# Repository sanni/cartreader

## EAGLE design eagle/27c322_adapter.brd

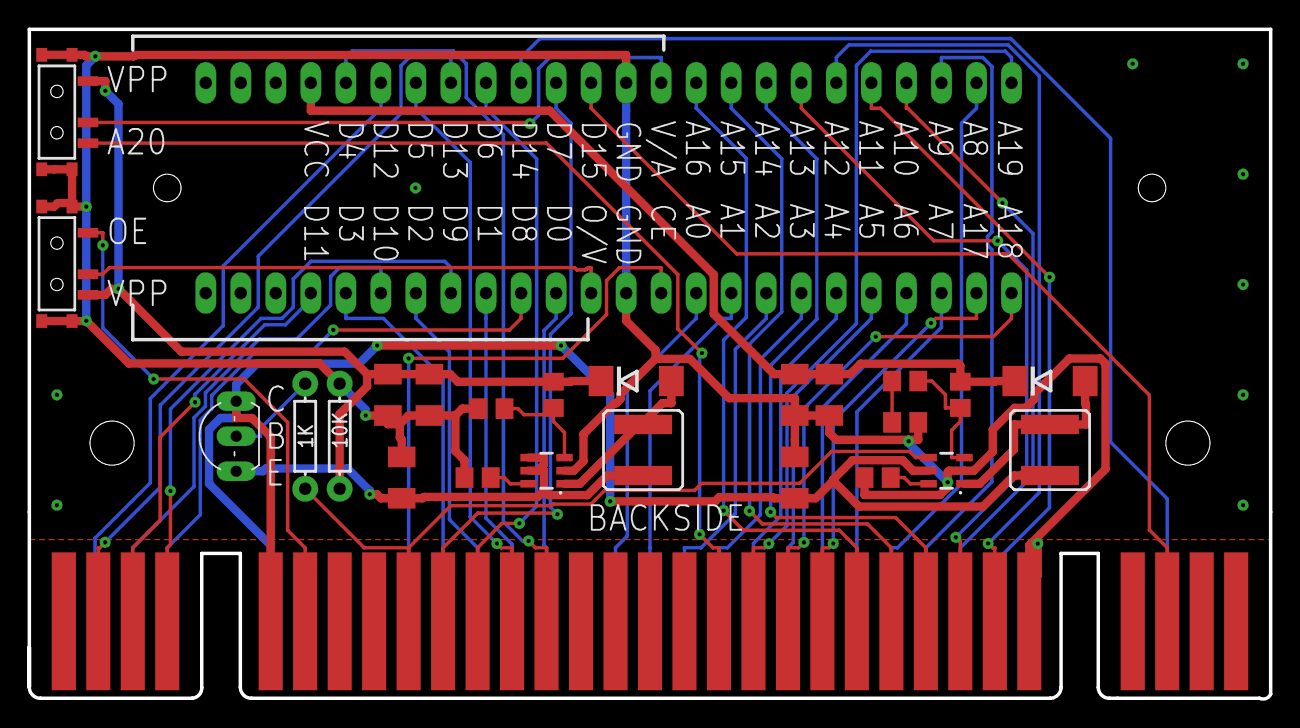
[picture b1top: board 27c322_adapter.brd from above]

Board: 2 copper layers, 90.0 x 48.6 mm, 26 parts (1 on the bottom side), 55 nets.

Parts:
C1, C2, C3, C4, C5, C6: C1206K
D1, D2: DO214AA
L1, L2: 47µH/±30%/750mA; CR54
OEVPP, OEVPP1: SMD-SWITCH
R1: 10K; AXIAL-0.3
R2: 1K; AXIAL-0.3
R3, R6: 30K; R0805
R4, R7: 10K; R0805
R5, R8: 191K; R0805
R10: 10k; R0805
STEPUP_VCC: MCP4725; SOT23-6
STEPUP_VPP: MCP4725; SOT23-6
T_VPP: TO92-CBE
U$1: CART-EXP-EDGE; CART-EXP-PINS-LONG
ZX1: 248-1282-00-0602J

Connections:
A0: U$1.17, ZX1.10
A1: U$1.16, ZX1.9
A2: U$1.15, ZX1.8
A3: U$1.14, ZX1.7
A4: U$1.13, ZX1.6
A5: U$1.12, ZX1.5
A6: U$1.11, ZX1.4
A7: U$1.10, ZX1.3
A8: U$1.9, ZX1.47
A9: U$1.8, ZX1.46
A10: U$1.7, ZX1.45
A11: U$1.6, ZX1.44
A12: U$1.37, ZX1.43
A13: U$1.38, ZX1.42
A14: U$1.39, ZX1.41
A15: U$1.40, ZX1.40
A16: U$1.41, ZX1.39
A17: U$1.42, ZX1.2
A18: U$1.43, ZX1.1
A19: U$1.44, ZX1.48
A20: OEVPP1.S, U$1.45
CE: U$1.23, ZX1.11
DQ0: U$1.19, ZX1.14
DQ1: U$1.20, ZX1.16
DQ2: U$1.21, ZX1.18
DQ3: U$1.22, ZX1.20
DQ4: U$1.50, ZX1.29
DQ5: U$1.51, ZX1.31
DQ6: U$1.52, ZX1.33
DQ7: U$1.53, ZX1.35
DQ8: U$1.28, ZX1.15
DQ9: U$1.59, ZX1.17
DQ10: U$1.29, ZX1.19
DQ11: U$1.60, ZX1.21
DQ12: U$1.30, ZX1.30
DQ13: U$1.61, ZX1.32
DQ14: U$1.3, ZX1.34
DQ15: U$1.34, ZX1.36
FB_VCC: R4.1, R5.1, STEPUP_VCC.3
FB_VPP: R7.1, R8.1, STEPUP_VPP.3
GND: C1.2, C2.2, C3.2, C4.2, C5.2, C6.2, OEVPP.P$1, OEVPP.P$2, OEVPP.P$3, OEVPP.P$4, OEVPP1.P$1, OEVPP1.P$2, OEVPP1.P$3, OEVPP1.P$4, R1.P$2, R3.2, R6.2, R7.2, R10.2, STEPUP_VCC.2, STEPUP_VPP.2, U$1.5, U$1.36, ZX1.12, ZX1.37
unnamed: R2.P$1, T_VPP.B
unnamed: R4.2, R10.1
NC_VCC: R3.1, STEPUP_VCC.6
NC_VPP: R6.1, STEPUP_VPP.6
OE: OEVPP.O, U$1.57
OEVPP: OEVPP.P, ZX1.13
SW_VCC: D1.A, L1.P$1, STEPUP_VCC.1
SW_VPP: D2.A, L2.P$1, STEPUP_VPP.1
VCC: C4.1, L1.P$2, STEPUP_VCC.5, T_VPP.C, U$1.27, U$1.58
VI_VPP: C1.1, L2.P$2, STEPUP_VPP.4, STEPUP_VPP.5, T_VPP.E
VO_VCC: C5.1, C6.1, D1.C, R5.2, ZX1.28
VO_VPP: C2.1, C3.1, D2.C, OEVPP.S, OEVPP1.O, R1.P$1, R8.2
VPPA20: OEVPP1.P, ZX1.38
WR: R2.P$2, STEPUP_VCC.4, U$1.54

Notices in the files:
parts and their libraries:
SparkFun-Coils: Licensing: Creative Commons ShareAlike 4.0 International - https://creativecommons.org/licenses/by-sa/4.0
